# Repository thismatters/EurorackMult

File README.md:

# Signal Multiplier

The signal mulitplier, as the name implies, multiplies signals. This module is an active mult, meaning that the input signal is buffered and the output duplicate signals are also individually buffered to ensure the signal is faithfully duplicated.

This is an original design featuring a three-layer stackup with a front face, a layer for all the jacks, and a power/processing layer where all the SMD components are layed out.

As with other modules in this line, this mult features:
* Polarity protection so that a backward power header doesn't fry anything (twin series schotty diodes: BAT54SL),
* Full surface mount design.

The KiCAD project here uses the library/footprints [found in my companion repo](https://github.com/thismatters/EurorackKiCAD).

## Width

12hp on an [Intellijel 1U rack](https://intellijel.com/support/1u-technical-specifications/).

## Inputs

There are two signal jacks, the lower one normals to the upper.

## Outputs

There are six output jacks with the top set being fed by the top input, and the bottom set being fed by the bottom input. If there is no jack plugged into the bottom input socket then the bottom outputs will output the upper input's signal.

## Adjustment

No adjustment required.

## Vendors

There are part numbers in the [BOM](mult.csv) for many of the parts (not for basic passives though) at the following vendors:

* [Mouser](https://www.mouser.com): Needs no introduction. Get your ICs from here (or [digikey](https://www.digikey.com)).
* [Tayda Electronics](https://www.taydaelectronics.com/): Good supplier for passive components; audio jacks, and potentiometers. Their audio jacks are slightly smaller than the thonkiconn from thonk.
* [Love My Switches](https://lovemyswitches.com/): Has [really good knobs](https://lovemyswitches.com/anodized-aluminum-knob-the-lo-fi-1-4-smooth-shaft-12-5mm-od/) to go on those potentiometers!
* [OSHPark](https://oshpark.com/): Fast and (relatively) cheap PCB manufacturer. The [V0 circuit](https://oshpark.com/shared_projects/0YTEwnCD) has some issues (outlined below), use at your own risk.

## Changelog

### V1
- Removed extra Op Amp and replaced a TL074 with TL072
- Removed several resistors
- Updated design language
- Added standoffs between component board and jack board (increased module width to accomodate)
- Fixed some other bugs

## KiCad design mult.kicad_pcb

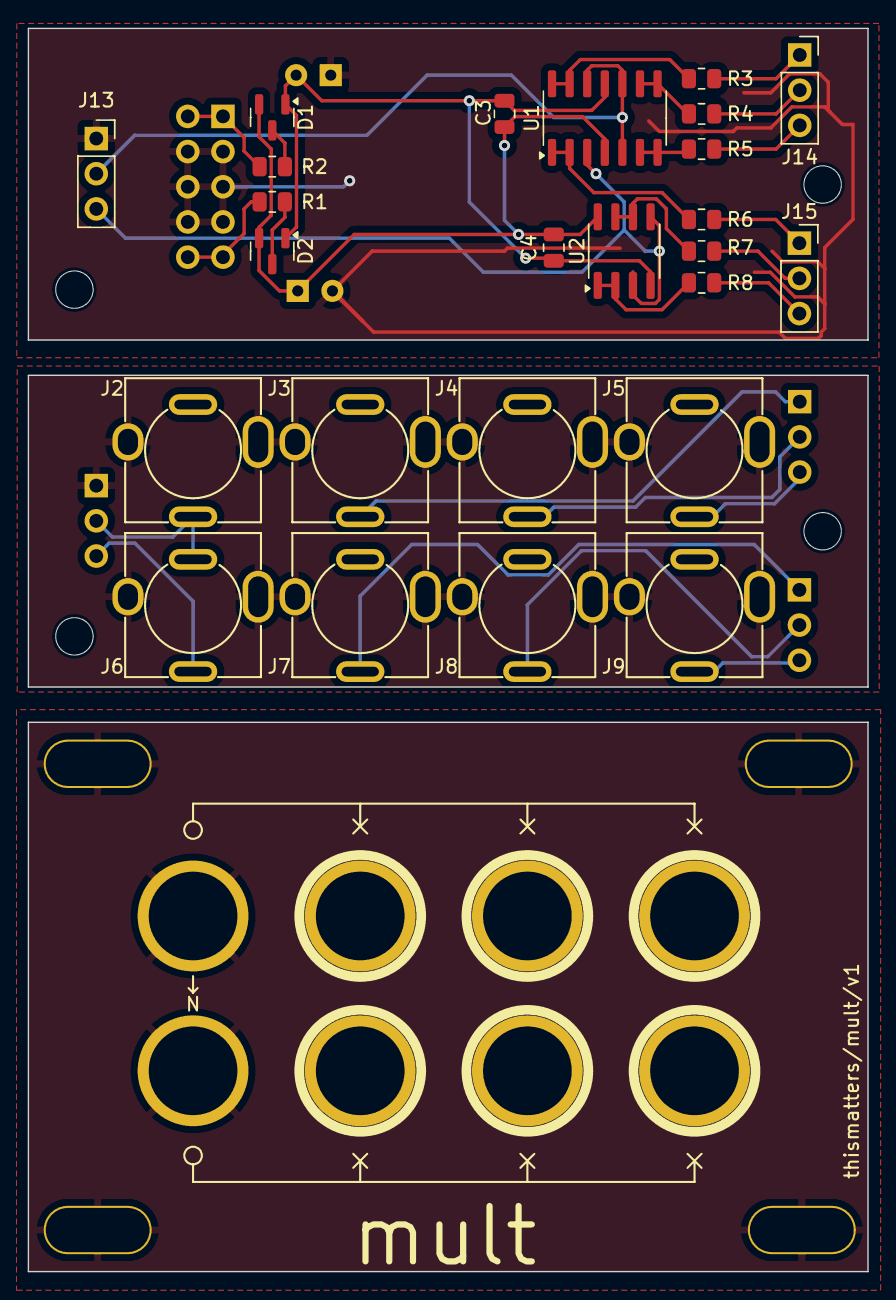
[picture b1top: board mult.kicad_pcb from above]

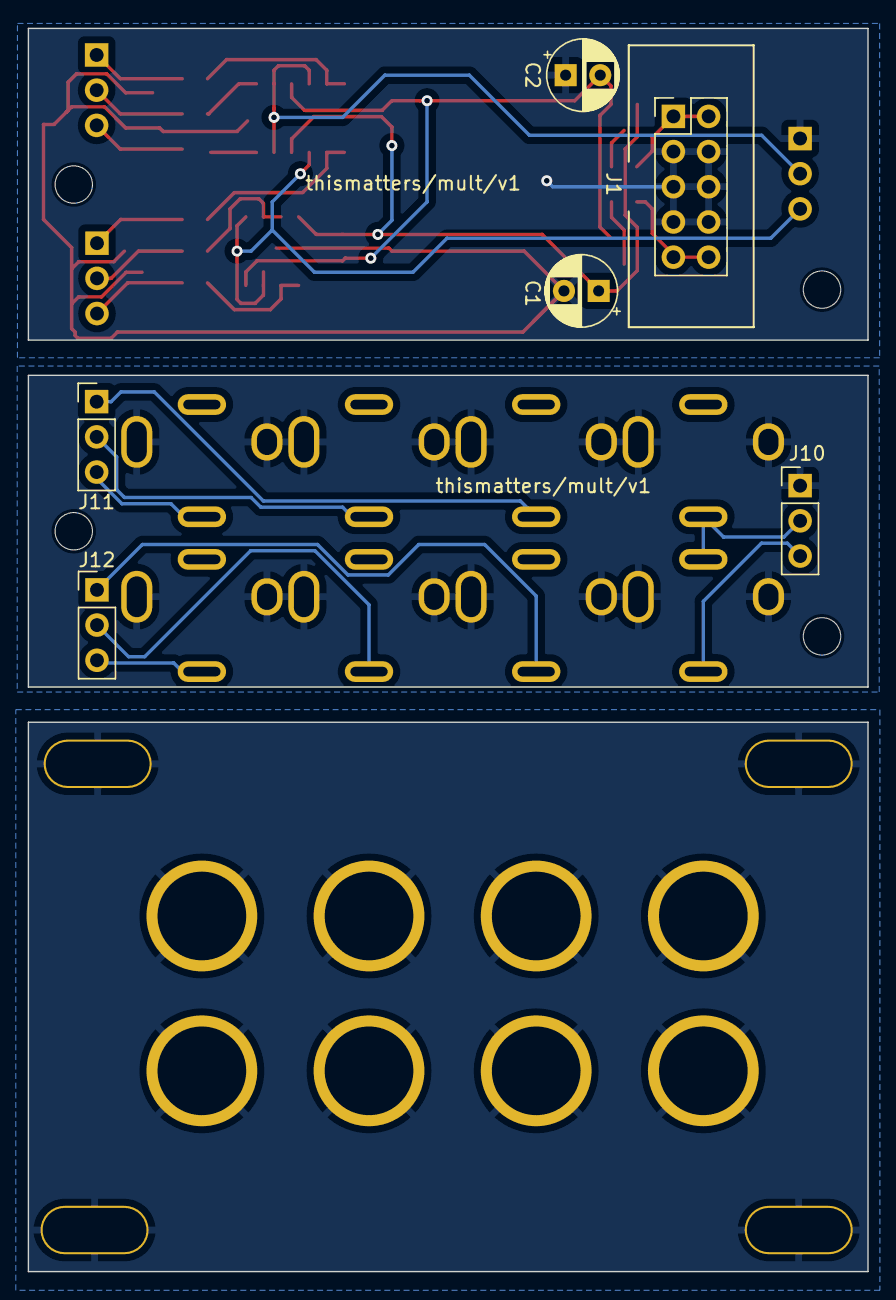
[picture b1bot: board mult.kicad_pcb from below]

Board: 2 copper layers, 60.6 x 89.7 mm, 47 parts (7 on the bottom side), 31 nets.

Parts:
C1, C2: 22u 50V; CP_Radial_D5.0mm_P2.50mm
C3, C4: 100n; C_0805_2012Metric
D1, D2: BAT54S; SOT-23
H1: mount0; Mech-MountingHole
H2: mount1; Mech-MountingHole
H3: mount2; Mech-MountingHole
H4: mount3; Mech-MountingHole
H5: in 1; Mech-AudioJack-Hole
H6: in 2; Mech-AudioJack-Hole
H7, H8, H9: out 1; Mech-AudioJack-Hole-Output
H10, H11, H12: out 2; Mech-AudioJack-Hole-Output
H13, H14, H15, H16: Standoff; MountingHole_2.7mm_M2.5
J1: Conn_02x05_Odd_Even; PinHeader_2x05_P2.54mm_Vertical
J2, J3, J4, J5, J6, J7, J8, J9: AudioJack2_SwitchT; AudioJack2_Tayda_A-2566
J10, J11, J12: Conn_01x03_Pin; PinHeader_1x03_P2.54mm_Vertical
J13, J14, J15: Conn_01x03_Socket; PinSocket_1x03_P2.54mm_Vertical
R1, R2: 10; R_0805_2012Metric
R3, R4, R5, R6, R7, R8: 1K; R_0805_2012Metric
U1: TL074; SOIC-14_3.9x8.7mm_P1.27mm
U2: TL072; SOIC-8_3.9x4.9mm_P1.27mm

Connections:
+12V: C1.1, C3.1, C4.1, D1.2 (K), D2.2 (K), U1.4 (V+), U2.8 (V+)
-12V: C2.2, C3.2, C4.2, D1.1 (A), D2.1 (A), U1.11 (V-), U2.4 (V-)
/FACE: H1.1, H2.1, H3.1, H4.1, H5.1, H6.1, H7.1, H8.1, H9.1, H10.1, H11.1, H12.1
/GND': J2.S, J3.S, J4.S, J5.S, J6.S, J7.S, J8.S, J9.S, J10.1
/IN0: J2.T, J6.TN, J10.2
/IN0': J13.2, U1.5 (+), U1.10 (+), U1.12 (+)
/IN1: J6.T, J10.3
/IN1': J13.3, U1.3 (+), U2.3 (+), U2.5 (+)
/OUT0: J3.T, J11.1
/OUT0': J14.1, R3.2
/OUT1: J4.T, J11.2
/OUT1': J14.2, R4.2
/OUT2: J5.T, J11.3
/OUT2': J14.3, R5.2
/OUT3: J7.T, J12.1
/OUT3': J15.1, R6.2
/OUT4: J8.T, J12.2
/OUT4': J15.2, R7.2
/OUT5: J9.T, J12.3
/OUT5': J15.3, R8.2
GND: C1.2, C2.1, J1.3, J1.4, J1.5, J1.6, J1.7, J1.8, J13.1
unnamed: D1.3 (COM), R2.1
unnamed: D2.3 (COM), R1.1
unnamed: J1.1, J1.2, R2.2
unnamed: J1.9, J1.10, R1.2
unnamed: R6.1, U1.1, U1.2 (-)
unnamed: R5.1, U1.6 (-), U1.7
unnamed: R4.1, U1.8, U1.9 (-)
unnamed: R3.1, U1.13 (-), U1.14
unnamed: R8.1, U2.1, U2.2 (-)
unnamed: R7.1, U2.6 (-), U2.7

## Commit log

2024-07-20 forgot to hit save
2024-08-13 Bugfixes from v0
2024-11-25 fixes readme
2025-04-26 prepping v1
